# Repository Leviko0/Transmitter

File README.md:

# Transmitter

Transmitter based on ESP32 and ESPNOW for a RC tracked vehicle. It utilizes the TI BQ24075 IC for power management, so the transmitter can switch between the battery as a power supply and the usb-c connector. It used the NCV68261 for reverse current and reverse polarity protection.

## Hardware overview

- **MCU:** ESP32-S3-WROOM-1
- **Power management:** TI BQ24075 for switching between battery and USB-C power.
- **Protection:** NCV68261 for reverse current/polarity protection
- **Regulator:** TPS63021 Buck-Boost, 3.3V rail
- **Input:** push buttons for vehicle control
- **Connectivity:** USB-C (USB 2.0) for charging/data, plus a header reserved for a display

Schematic:

PCB:
PCB is still a work in progress

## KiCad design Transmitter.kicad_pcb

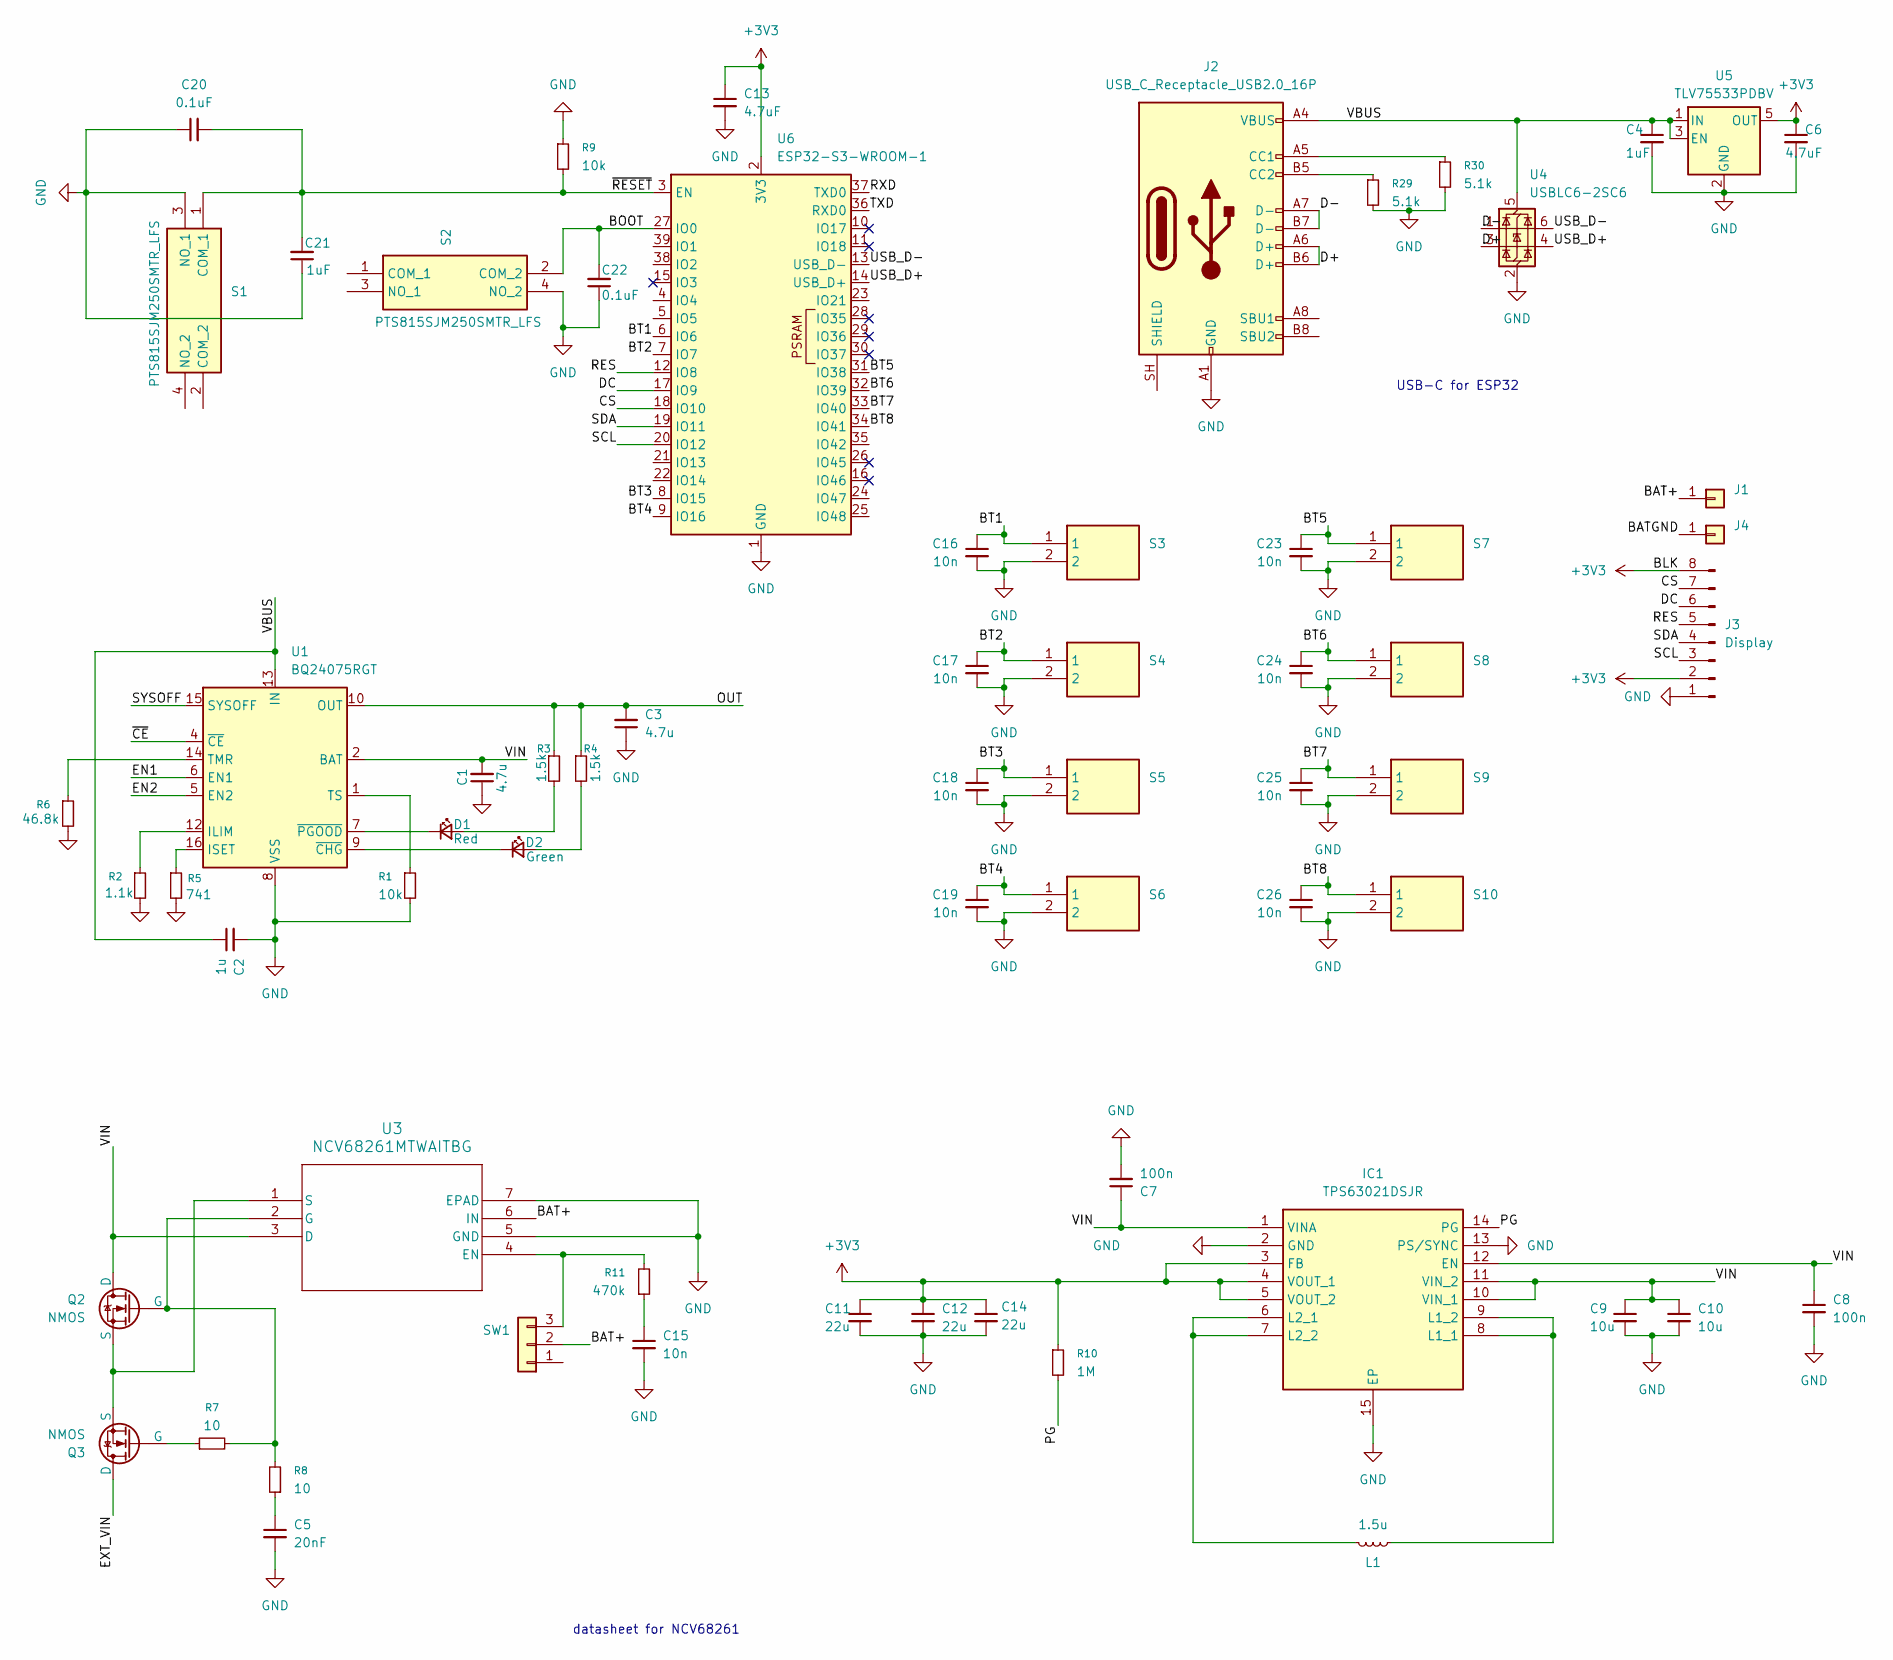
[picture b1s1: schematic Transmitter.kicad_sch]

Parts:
C1, C3: 4.7u; C_0603_1608Metric
C2: 1u; C_0603_1608Metric
C4, C21: 1uF; C_0603_1608Metric
C5: 20nF; C_0603_1608Metric
C6, C13: 4.7uF; C_0603_1608Metric
C7, C8: 100n; C_0603_1608Metric
C9, C10: 10u; C_0805_2012Metric
C11, C12, C14: 22u; C_0805_2012Metric
C15, C16, C17, C18, C19, C23, C24, C25, C26: 10n; C_0603_1608Metric
C20, C22: 0.1uF; C_0603_1608Metric
D1: Red; LED_0603_1608Metric
D2: Green; LED_0603_1608Metric
IC1: TPS63021DSJR; SON50P300X400X100-15N-D; Mouser Part Number 595-TPS63021DSJR
J1, J4: Conn_01x01; SolderWirePad_1x01_SMD_3x6mm
J2: USB_C_Receptacle_USB2.0_16P; USB494000A
J3: Display; PinHeader_1x08_P2.54mm_Vertical
L1: 1.5u; INDPM4441X120N
Q2, Q3: NMOS; TO-263-3_TabPin2
R1, R9: 10k; R_0603_1608Metric
R2: 1.1k; R_0603_1608Metric
R3, R4: 1.5k; R_0603_1608Metric
R5: 741; R_0603_1608Metric
R6: 46.8k; R_0603_1608Metric
R7, R8: 10; R_0603_1608Metric
R10: 1M; R_0603_1608Metric
R11: 470k; R_0603_1608Metric
R29, R30: 5.1k; R_0603_1608Metric
S1, S2: PTS815SJM250SMTR_LFS; PTS815SJM250SMTRLFS; Manufacturer_Part_Number PTS815SJM250SMTR LFS; Mouser Part Number 611-PTS815SJM250SMTR
S3, S4, S5, S6, S7, S8, S9, S10: TLSA040T3JLFS; Manufacturer_Part_Number TLSA040T3JLFS
SW1: Conn_01x03; PinHeader_1x03_P2.54mm_Vertical
U1: BQ24075RGT; VQFN-16-1EP_3x3mm_P0.5mm_EP1.6x1.6mm
U3: NCV68261MTWAITBG; WDFNW6_511DW_ONS_OSI
U4: USBLC6-2SC6; SOT-23-6
U5: TLV75533PDBV; SOT-23-5
U6: ESP32-S3-WROOM-1

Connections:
+3V3: C6.1, C11.1, C12.1, C13.1, C14.1, IC1.3 (FB), IC1.4 (VOUT_1), IC1.5 (VOUT_2), J3.2, J3.8, R10.1, U5.5 (OUT), U6.2 (3V3)
/BAT+: J1.1 (Pin_1_1), SW1.2, U3.6 (IN)
/BATGND: J4.1 (Pin_1_1)
/BOOT: C22.2, S2.2 (COM_2), U6.27 (IO0)
/BT1: C16.1, S3.1, U6.6 (IO6)
/BT2: C17.1, S4.1, U6.7 (IO7)
/BT3: C18.1, S5.1, U6.8 (IO15)
/BT4: C19.1, S6.1, U6.9 (IO16)
/BT5: C23.1, S7.1, U6.31 (IO38)
/BT6: C24.1, S8.1, U6.32 (IO39)
/BT7: C25.1, S9.1, U6.33 (IO40)
/BT8: C26.1, S10.1, U6.34 (IO41)
/CS: J3.7, U6.18 (IO10)
/D+: J2.A6 (D+), J2.B6 (D+), U4.3 (I/O2)
/D-: J2.A7 (D-), J2.B7 (D-), U4.1 (I/O1)
/DC: J3.6, U6.17 (IO9)
/EN1: U1.6 (EN1)
/EN2: U1.5 (EN2)
/EXT_VIN: Q3.2 (D)
/OUT: C3.2, R3.1, R4.1, U1.10 (OUT), U1.11 (OUT)
/PG: IC1.14 (PG), R10.2
/RES: J3.5, U6.12 (IO8)
/RXD: U6.37 (TXD0)
/SCL: J3.3, U6.20 (IO12)
/SDA: J3.4, U6.19 (IO11)
/SYSOFF: U1.15 (SYSOFF)
/TXD: U6.36 (RXD0)
/USB_D+: U4.4 (I/O2), U6.14 (USB_D+)
/USB_D-: U4.6 (I/O1), U6.13 (USB_D-)
/VBUS: C2.1, C4.1, J2.A4 (VBUS), J2.A9 (VBUS), J2.B4 (VBUS), J2.B9 (VBUS), U1.13 (IN), U4.5 (VBUS), U5.1 (IN), U5.3 (EN)
/VIN: C1.2, C7.1, C8.1, C9.1, C10.1, IC1.1 (VINA), IC1.10 (VIN_1), IC1.11 (VIN_2), IC1.12 (EN), Q2.2 (D), U1.2 (BAT), U1.3 (BAT), U3.3 (D)
/~CE: U1.4 (~CE)
/~RESET: C20.2, C21.2, R9.2, S1.1 (COM_1), U6.3 (EN)
GND: C1.1, C2.2, C3.1, C4.2, C5.2, C6.2, C7.2, C8.2, C9.2, C10.2, C11.2, C12.2, C13.2, C14.2, C15.2, C16.2, C17.2, C18.2, C19.2, C20.1, C21.1, C22.1, C23.2, C24.2, C25.2, C26.2, IC1.2 (GND), IC1.13 (PS/SYNC), IC1.15 (EP), J2.A1 (GND), J2.A12 (GND), J2.B1 (GND), J2.B12 (GND), J3.1, R1.2, R2.2, R5.2, R6.2, R9.1, R29.2, R30.2, S1.3 (NO_1), S2.4 (NO_2), S3.2, S4.2, S5.2, S6.2, S7.2, S8.2, S9.2, S10.2, U1.8 (VSS), U1.17 (VSS), U3.5 (GND), U3.7 (EPAD), U4.2 (GND), U5.2 (GND), U6.1 (GND), U6.40 (GND), U6.41 (GND)
unnamed: C5.1, R8.1
unnamed: C15.1, R11.1
unnamed: D1.2 (A), R3.2
unnamed: D1.1 (K), U1.7 (~PGOOD)
unnamed: D2.2 (A), R4.2
unnamed: D2.1 (K), U1.9 (~CHG)
unnamed: IC1.8 (L1_1), IC1.9 (L1_2), L1.1
unnamed: IC1.6 (L2_1), IC1.7 (L2_2), L1.2
unnamed: J2.A5 (CC1), R30.1
unnamed: J2.B5 (CC2), R29.1
unnamed: Q2.1 (G), R7.2, R8.2, U3.2 (G)
unnamed: Q2.3 (S), Q3.3 (S), U3.1 (S)
unnamed: Q3.1 (G), R7.1
unnamed: R11.2, SW1.3, U3.4 (EN)
unnamed: R2.1, U1.12 (ILIM)
unnamed: R5.1, U1.16 (ISET)
unnamed: R6.1, U1.14 (TMR)
unnamed: R1.1, U1.1 (TS)

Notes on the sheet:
datasheet for NCV68261
USB-C for ESP32

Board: 2 copper layers, 65 parts (0 on the bottom side), 44 nets, no tracks yet.
